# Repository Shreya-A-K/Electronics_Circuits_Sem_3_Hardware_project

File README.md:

<h1> Potentiometer-Controlled Differential Amplifier Comparator Project </h1>

This project demonstrates the working of a BJT-based differential amplifier as a DC voltage comparator.
Two potentiometers are used to create adjustable voltage dividers, providing independent input signals to the bases of the two transistors.

By adjusting the potentiometer values, you can vary the base voltages.

The transistor receiving the higher base voltage conducts more current, turning its LED ON.

The other transistor remains OFF (or dim), showing the comparator action.

This makes it easy to visualize how a differential amplifier compares two DC input signals without requiring oscilloscopes or complex equipment.

<h2>Application:</h2>
This forms the input stage of Op- Amp (Differential Amplifier)

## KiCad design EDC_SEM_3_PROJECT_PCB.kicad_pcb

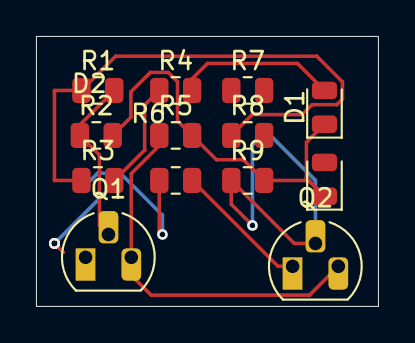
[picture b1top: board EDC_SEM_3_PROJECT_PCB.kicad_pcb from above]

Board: 2 copper layers, 19.0 x 15.0 mm, 13 parts (0 on the bottom side), 9 nets.

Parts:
D1, D2: LED; LED_0805_2012Metric
Q1, Q2: NPN; TO-92L_HandSolder
R1, R2, R4, R7, R9: 1000R; R_0805_2012Metric
R3, R6: 10000R; R_0805_2012Metric
R5: 470R; R_0805_2012Metric
R8: 1R; R_0805_2012Metric

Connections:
+9V: R1.1, R3.1, R6.1, R8.1
GND: D1.1 (K), D2.1 (K), R2.2, R5.2, R9.2
unnamed: D1.2 (A), R4.2
unnamed: D2.2 (A), R7.2
unnamed: Q1.2 (B), R1.2, R2.1
unnamed: Q1.1 (C), R3.2, R4.1
unnamed: Q1.3 (E), Q2.3 (E), R5.1
unnamed: Q2.2 (B), R8.2, R9.1
unnamed: Q2.1 (C), R6.2, R7.1

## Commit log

2025-09-21 Create Simulation_link
2025-09-21 Rename circuit-20250921-2156.png to Circuit_diagram.png
2025-12-02 Rename image.png to PCB_design.png
